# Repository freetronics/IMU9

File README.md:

IMU9
====
http://www.freetronics.com/products/9-dof-imu-accelerometer-gyroscope-magnetometer

Design files for the Freetronics IMU9 - a 9-DOF IMU with I2C interface.

Combining an accelerometer, a magnetometer, and a gyroscope all in one tiny package with an Arduino-friendly I2C interface.

Perfect for building an autopilot for a quadcopter, or tracking the position of a robot, or logging data in a rocket. Combine three axis data from each of the sensors for a total of 9 degrees-of-freedom (DOF) of tracking.

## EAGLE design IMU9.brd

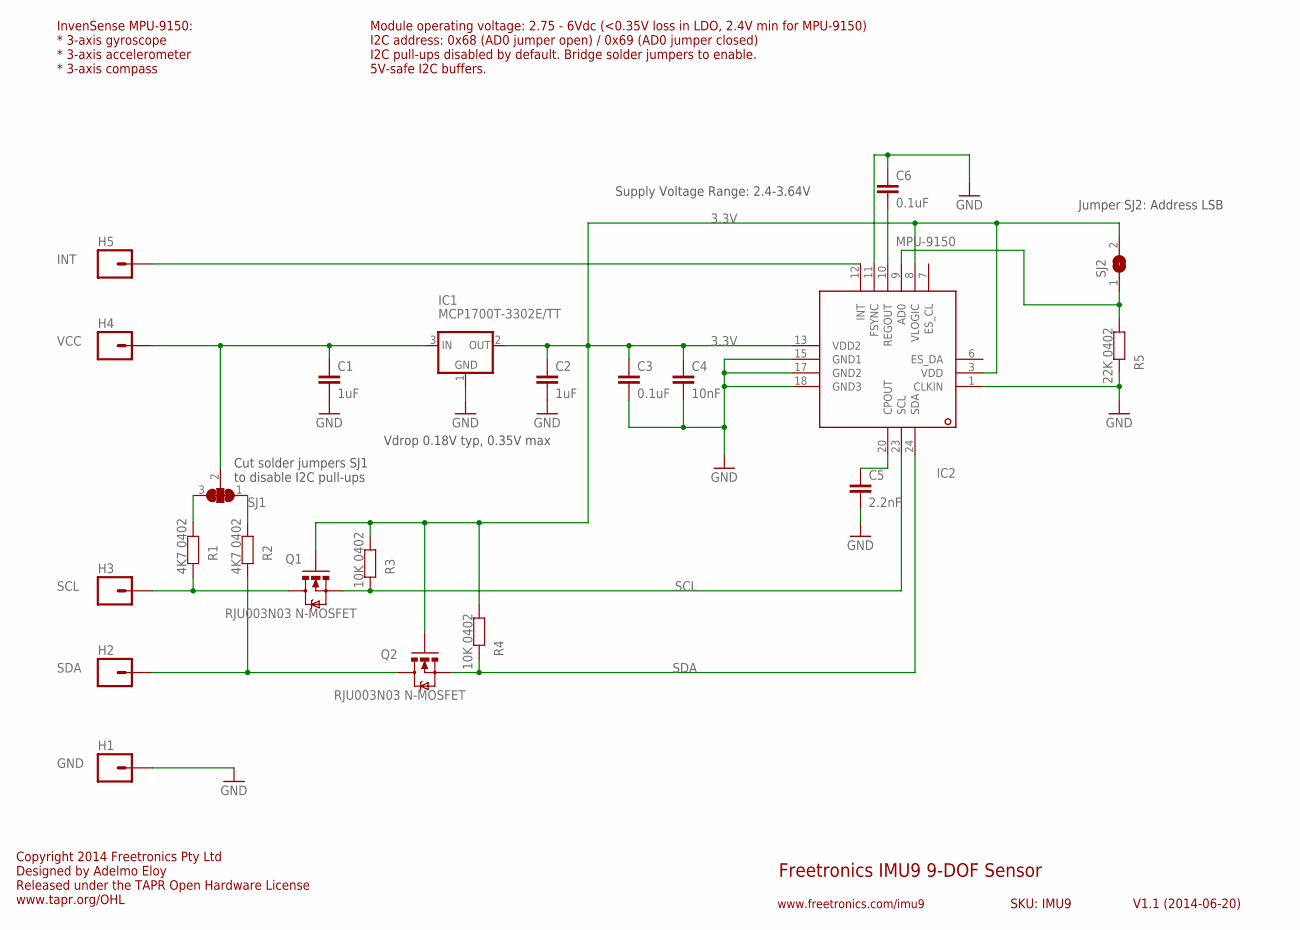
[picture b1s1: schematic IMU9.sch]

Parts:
C1, C2: 1uF; 0603
C3, C6: 0.1uF; 0603
C4: 10nF; 0603
C5: 2.2nF; 0603
H1: GND; 1X01
H2: SDA; 1X01
H3: SCL; 1X01
H4: VCC; 1X01
H5: INT; 1X01
IC1: MCP1700T-3302E/TT; SOT23-3
IC2: MPU-9150; QFN-24MPU
Q1, Q2: RJU003N03 N-MOSFET; SOT32-3
R1, R2: 4K7 0402; 0402
R3, R4: 10K 0402; 0402
R5: 22K 0402; 0402
SJ1: SJ2W; SJ_2
SJ2: SJ

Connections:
3.3V: C2.1, C3.1, C4.1, IC1.2 (OUT), IC2.3 (VDD), IC2.8 (VLOGIC), IC2.13 (VDD2), Q1.1 (G), Q2.1 (G), R3.2, R4.2, SJ2.2
GND: C1.2, C2.2, C3.2, C4.2, C5.2, C6.1, H1.1, IC1.1 (GND), IC2.1 (CLKIN), IC2.11 (FSYNC), IC2.15 (GND1), IC2.17 (GND2), IC2.18 (GND3), R5.1
unnamed: IC2.23 (SCL), Q1.2 (S), R3.1
unnamed: C5.1, IC2.20 (CPOUT)
unnamed: C1.1, H4.1, IC1.3 (IN), SJ1.2
unnamed: IC2.24 (SDA), Q2.2 (S), R4.1
unnamed: R1.2, SJ1.3
unnamed: R2.2, SJ1.1
unnamed: C6.2, IC2.10 (REGOUT)
unnamed: IC2.9 (AD0), R5.2, SJ2.1
unnamed: H5.1, IC2.12 (INT)
SCL: H3.1, Q1.3 (D), R1.1
SDA: H2.1, Q2.3 (D), R2.1

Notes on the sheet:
Freetronics IMU9 9-DOF Sensor
V1.1 (2014-06-20)
www.freetronics.com/imu9
SKU: IMU9
Supply Voltage Range: 2.4-3.64V
Cut solder jumpers SJ1 to disable I2C pull-ups
Vdrop 0.18V typ, 0.35V max
Jumper SJ2: Address LSB
Copyright 2014 Freetronics Pty Ltd Designed by Adelmo Eloy Released under the TAPR Open Hardware License www.tapr.org/OHL
InvenSense MPU-9150: * 3-axis gyroscope * 3-axis accelerometer * 3-axis compass
Module operating voltage: 2.75 - 6Vdc (<0.35V loss in LDO, 2.4V min for MPU-9150) I2C address: 0x68 (AD0 jumper open) / 0x69 (AD0 jumper closed) I2C pull-ups disabled by default. Bridge solder jumpers to enable. 5V-safe I2C buffers.

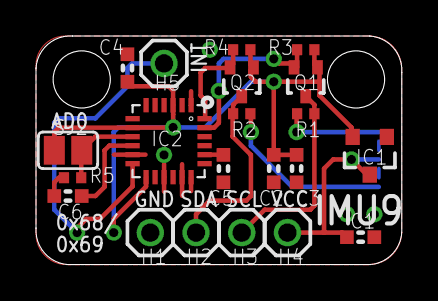
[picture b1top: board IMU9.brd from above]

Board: 2 copper layers, 20.3 x 12.7 mm, 22 parts (1 on the bottom side), 13 nets.

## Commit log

2013-12-21 Initial project.
2014-01-21 Added Adelmo Eloy as designer Added notes to schematic about max parameters Improved silkscreen Improved designator positions Improved part designators and values
2014-06-20 Bridged across I2C pull-up cut track jumpers Shortened URL
2014-10-07 Add schematic PDF
2014-10-07 Add README

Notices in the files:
IMU9.brd:
(c) 2014 Freetronics
parts and their libraries:
freetronics-original: Licensing: CC v3.0 Share-Alike You are welcome to use this library for commercial purposes.
